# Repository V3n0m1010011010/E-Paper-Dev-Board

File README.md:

# ESP32 E-Paper Board

Eine kompakte, selbst entwickelte ESP32-S3-Platine für portable Anwendungen mit E-Paper-Display, microSD-Karte, Navigationstaster und LiPo-Akku.

## Features

- ESP32-S3-WROOM-1U
- 1.54" E-Paper Display
- microSD-Karten-Slot
- 3-Wege-Navigationstaster
  - UP
  - DOWN
  - PUSH
- USB-C für Stromversorgung, Programmierung und serielle Kommunikation
- 3.7 V LiPo-Akku
- Integrierter LiPo-Ladecontroller
- 3.3 V Spannungsversorgung
- Kompakte Bauform

## 3D-Modell

### Oberseite

### Unterseite

## Verwendete Komponenten

| Komponente | Beschreibung |
|---|---|
| ESP32-S3-WROOM-1U | Hauptcontroller |
| GDEY0154D67 | 1.54" E-Paper Display |
| BQ25896 | LiPo-Ladecontroller |
| TPS62843 | 3.3 V Buck-Converter |
| TS43-135255-10-BK-200-SMT-TR | Navigationstaster |
| USB4105 | USB-C Anschluss |
| SM02B-SRSS-TB(LF)(SN) | JST-Akkuanschluss |

## Dokumentation

Die verwendeten Datenblätter befinden sich im Ordner [`Docs`](./esp32_epaper_board/Docs/).

Enthalten sind unter anderem die Datenblätter für:

- [ESP32-S3-WROOM-1U](./esp32_epaper_board/Docs/ESP32-S3-WROOM-1U-N8_Espressif_Systems.pdf)
- [GDEY0154D67 E-Paper Display](./esp32_epaper_board/Docs/GDEY0154D67-new.pdf)
- [BQ25896 LiPo-Ladecontroller](./esp32_epaper_board/Docs/bq25896.pdf)
- [TPS62843 Spannungsregler](./esp32_epaper_board/Docs/tps62843.pdf)
- [TS43-135255-10-BK-200-SMT-TR Navigationstaster](./esp32_epaper_board/Docs/TS43-135255-10-BK-200-SMT-TR_Same_Sky.pdf)
- [USB4105 USB-C Anschluss](./esp32_epaper_board/Docs/usb4105.pdf)
- [SM02B-SRSS JST Anschluss](./esp32_epaper_board/Docs/SM02B-SRSS-TB(LF)(SN)_JST_Sales.pdf)

Die übrigen Dateien im `Docs`-Ordner enthalten zusätzliche Datenblätter und Referenzinformationen für das PCB-Design.

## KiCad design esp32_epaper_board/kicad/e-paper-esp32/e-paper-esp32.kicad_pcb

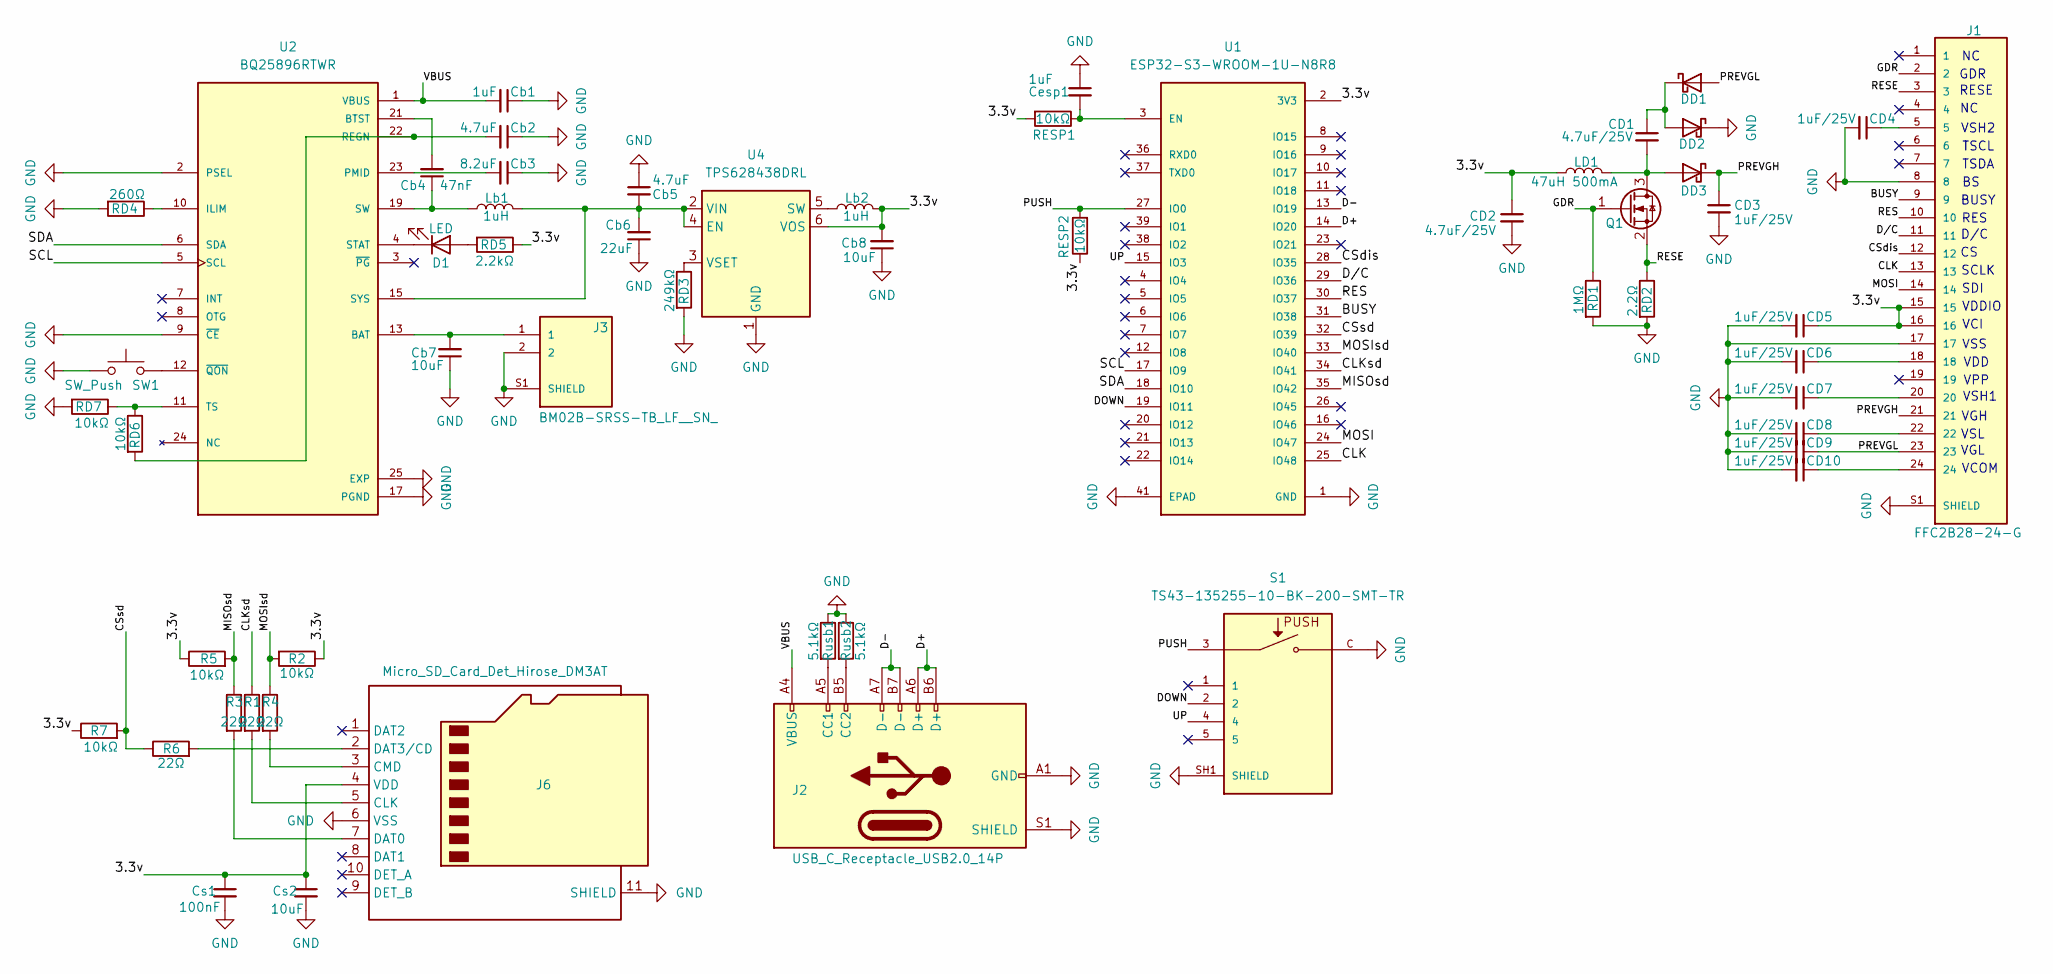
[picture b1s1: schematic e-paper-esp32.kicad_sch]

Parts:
CD1, CD2: 4.7uF/25V; C_0603_1608Metric
CD3, CD4, CD5, CD6, CD7, CD8, CD9, CD10: 1uF/25V; C_0603_1608Metric
Cb1: 1uF; C_0603_1608Metric
Cb2, Cb5: 4.7uF; C_0603_1608Metric
Cb3: 8.2uF; C_0603_1608Metric
Cb4: 47nF; C_0603_1608Metric
Cb6: 22uF; C_0603_1608Metric
Cb7, Cb8: 10uF; C_0603_1608Metric
Cesp1: 1uF; C_0603_1608Metric
Cs1: 100nF; C_0603_1608Metric
Cs2: 10uF; C_0603_1608Metric
D1: LED; LED_0201_0603Metric
DD1, DD2, DD3: MBR0530; D_SOD-123
J1: FFC2B28-24-G; GCT_FFC2B28-24-G; PARTREV A
J2: USB_C_Receptacle_USB2.0_14P; USB_C_Receptacle_GCT_USB4105-xx-A_16P_TopMnt_Horizontal
J3: BM02B-SRSS-TB_LF__SN_; SM02B-SRSS-TB_LF__SN; PARTREV N/A
J6: Micro_SD_Card_Det_Hirose_DM3AT; microSD_HC_Hirose_DM3AT-SF-PEJM5
LD1: 47uH 500mA; L_0805_2012Metric
Lb1, Lb2: 1uH; L_0805_2012Metric
Q1: Si1308EDL; SOT-323_SC-70
R1, R3, R4, R6: 22Ω; R_0603_1608Metric
R2, R5, R7: 10kΩ; R_0603_1608Metric
RD1: 1MΩ; R_0603_1608Metric
RD2: 2.2Ω; R_0603_1608Metric
RD3: 249kΩ; R_0603_1608Metric
RD4: 260Ω; R_0603_1608Metric
RD5: 2.2kΩ; R_0603_1608Metric
RD6, RD7: 10kΩ; R_0603_1608Metric
RESP1, RESP2: 10kΩ; R_0603_1608Metric
Rusb1, Rusb2: 5.1kΩ; R_0603_1608Metric
S1: TS43-135255-10-BK-200-SMT-TR; SW_TS43-135255-10-BK-200-SMT-TR
SW1: SW_Push; SW_Push_SPST_NO_Alps_SKRK
U1: ESP32-S3-WROOM-1U-N8R8; ESP32-S3-WROOM-1U; PARTREV v1.1
U2: BQ25896RTWR; IC_BQ25896RTWR; PARTREV C
U4: TPS628438DRL; SOT-563

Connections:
/3.3v: CD2.1, CD5.1, Cb8.2, Cs1.1, Cs2.1, J1.15, J1.16, J6.4 (VDD), LD1.2, Lb2.1, R2.1, R5.1, R7.1, RD5.1, RESP1.2, RESP2.1, U1.2 (3V3), U4.6 (VOS)
/BUSY: J1.9, U1.31 (IO38)
/CLK: J1.13, U1.25 (IO48)
/CLKsd: R1.1, U1.34 (IO41)
/CSdis: J1.12, U1.28 (IO35)
/CSsd: R6.1, R7.2, U1.32 (IO39)
/D+: J2.A6 (D+), J2.B6 (D+), U1.14 (IO20)
/D-: J2.A7 (D-), J2.B7 (D-), U1.13 (IO19)
/DOWN: S1.2, U1.19 (IO11)
/D/C: J1.11, U1.29 (IO36)
/GDR: J1.2, Q1.1 (G), RD1.1
/MISOsd: R3.1, R5.2, U1.35 (IO42)
/MOSI: J1.14, U1.24 (IO47)
/MOSIsd: R2.2, R4.1, U1.33 (IO40)
/PREVGH: CD3.1, DD3.1 (K), J1.21
/PREVGL: CD9.1, DD1.2 (A), J1.23
/PUSH: RESP2.2, S1.3, U1.27 (IO0)
/RES: J1.10, U1.30 (IO37)
/RESE: J1.3, Q1.2 (S), RD2.1
/SCL: U1.17 (IO9), U2.5 (SCL)
/SDA: U1.18 (IO10), U2.6 (SDA)
/UP: S1.4, U1.15 (IO3)
/VBUS: Cb1.2, J2.A4 (VBUS), J2.A9 (VBUS), J2.B4 (VBUS), J2.B9 (VBUS), U2.1 (VBUS)
GND: CD2.2, CD3.2, CD4.2, CD5.2, CD6.2, CD7.2, CD8.2, CD9.2, CD10.2, Cb1.1, Cb2.1, Cb3.1, Cb5.1, Cb6.1, Cb7.1, Cb8.1, Cesp1.1, Cs1.2, Cs2.2, DD2.1 (K), J1.8, J1.17, J1.S1 (SHIELD), J1.S2 (SHIELD), J2.A1 (GND), J2.A12 (GND), J2.B1 (GND), J2.B12 (GND), J2.S1 (SHIELD), J3.2, J3.S1 (SHIELD), J3.S2 (SHIELD), J6.6 (VSS), J6.11 (SHIELD), RD1.2, RD2.2, RD3.2, RD4.2, RD7.2, Rusb1.1, Rusb2.1, S1.C, S1.SH1 (SHIELD), S1.SH2 (SHIELD), S1.SH3 (SHIELD), S1.SH4 (SHIELD), S1.SH5 (SHIELD), S1.SH6 (SHIELD), SW1.1, U1.1 (GND), U1.40 (GND), U1.41 (EPAD), U1.41_1 (GND), U1.41_2 (GND), U1.41_3 (GND), U1.41_4 (GND), U1.41_5 (GND), U1.41_6 (GND), U1.41_7 (GND), U1.41_8 (GND), U1.41_9 (GND), U2.2 (PSEL), U2.9 (~CE), U2.17 (PGND), U2.18 (PGND), U2.25 (EXP), U4.1 (GND)
unnamed: CD4.1, J1.5
unnamed: CD6.1, J1.18
unnamed: CD7.1, J1.20
unnamed: CD8.1, J1.22
unnamed: CD10.1, J1.24
unnamed: Cb4.1, Lb1.2, U2.19 (SW), U2.20 (SW)
unnamed: Cb7.2, J3.1, U2.13 (BAT), U2.14 (BAT)
unnamed: D1.2 (A), RD5.2
unnamed: D1.1 (K), U2.4 (STAT)
unnamed: CD1.1, DD1.1 (K), DD2.2 (A)
unnamed: CD1.2, DD3.2 (A), LD1.1, Q1.3 (D)
unnamed: J2.A5 (CC1), Rusb1.2
unnamed: J2.B5 (CC2), Rusb2.2
unnamed: J6.5 (CLK), R1.2
unnamed: J6.3 (CMD), R4.2
unnamed: J6.7 (DAT0), R3.2
unnamed: J6.2 (DAT3/CD), R6.2
unnamed: Cesp1.2, RESP1.1, U1.3 (EN)
unnamed: Cb4.2, U2.21 (BTST)
unnamed: RD4.1, U2.10 (ILIM)
unnamed: Cb3.2, U2.23 (PMID)
unnamed: Cb2.2, RD6.2, U2.22 (REGN)
unnamed: RD6.1, RD7.1, U2.11 (TS)
unnamed: SW1.2, U2.12 (~QON)
unnamed: Cb5.2, Cb6.2, Lb1.1, U2.15 (SYS), U2.16 (SYS), U4.2 (VIN), U4.4 (EN)
unnamed: Lb2.2, U4.5 (SW)
unnamed: RD3.1, U4.3 (VSET)

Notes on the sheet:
BUSY
VGH
GDR
VSH2
VDD
SDI
VSH1
TSCL
RES
VSS
VCI
VCOM
SCLK
VPP
RESE
VGL
D/C
VDDIO
VSL
TSDA

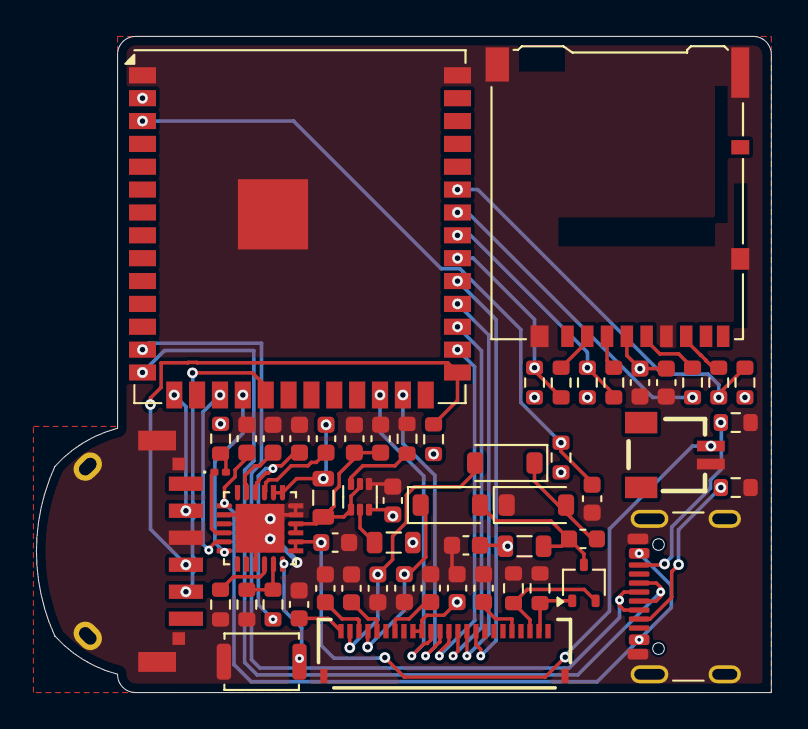
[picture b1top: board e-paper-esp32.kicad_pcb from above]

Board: 2 copper layers, 40.8 x 36.4 mm, 56 parts (0 on the bottom side), 51 nets.
